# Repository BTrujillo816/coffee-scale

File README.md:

# ECET 430 Project: Digital Coffee Scale

This is a project for NJIT's ECET 430 - Electronics Manufacturing class.

## Purpose

This digital coffee scale will display weight measurements, flow rate, and include a built-in timer. It will also be able to send brew parameters through WiFi or Bluetooth to an App or other interface.

## Repo Layout

- `hardware` KiCad project with schematic, pcb layout, plots, drawings
- `software` ESP32 firmware and Arduino IDE setup
- `documentation` Technical documentation and user manual
- `logbook` Markdown files for progress updates

## Usage

See the [user documentation](documentation/UserDocumentation.md).

## Design

See the [design decision document](documentation/DesignDecisions.md).

## Credit

This project was made possible by borrowing from great designs, including:

- ABC's wearable widget, https://github.com/example/project
- XYZ's battery management, https://github.com/example/otherproject

## Author

Written by Brandon Trujillo and Miguel Takinan, 2024

## License

This work is available under the [Creative Commons Attribution-ShareAlike License 4.0](https://en.wikipedia.org/wiki/Wikipedia:Text_of_the_Creative_Commons_Attribution-ShareAlike_4.0_International_License). A local copy is available at [LICENSE.md](LICENSE.md).

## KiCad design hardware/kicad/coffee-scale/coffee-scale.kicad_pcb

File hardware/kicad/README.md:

# Digital Coffee Scale KiCad Project

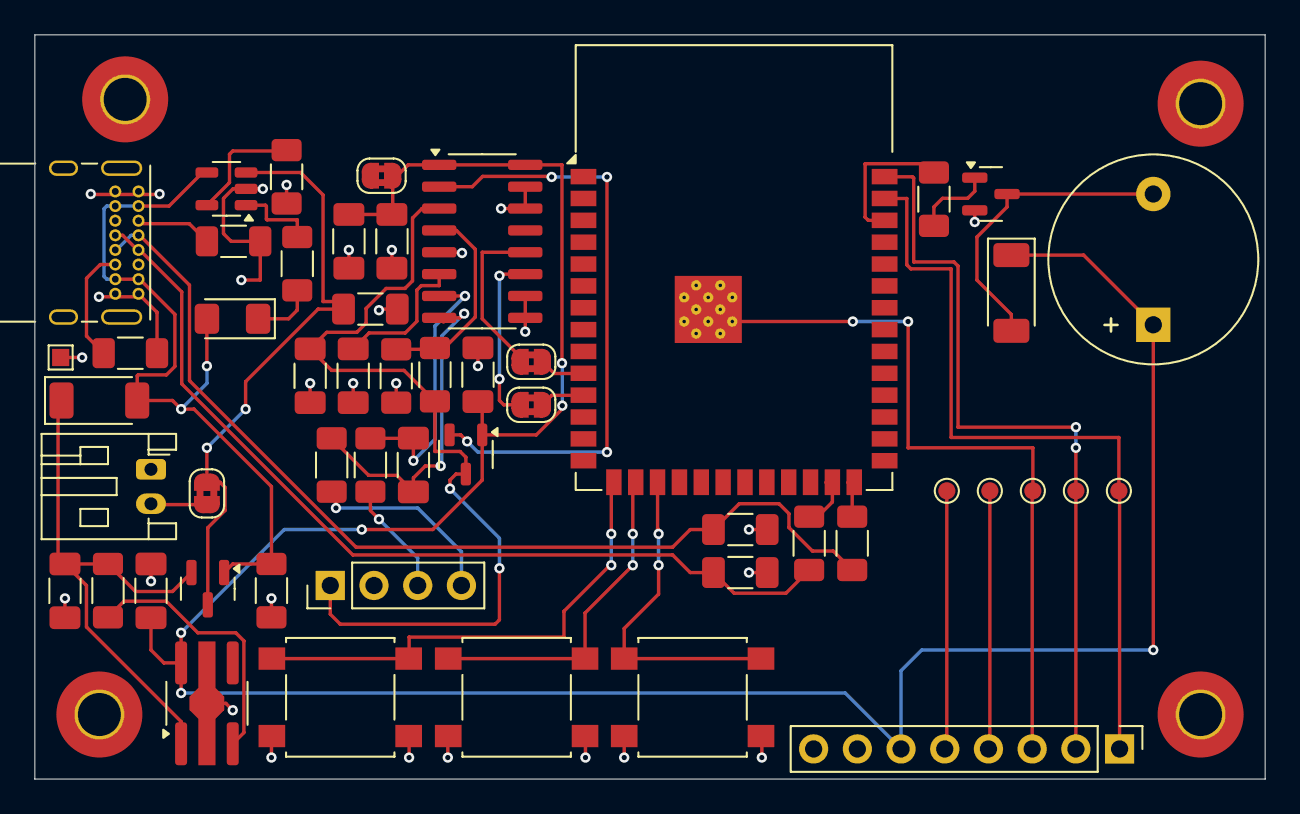
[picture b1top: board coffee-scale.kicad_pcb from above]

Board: 2 copper layers, 71.5 x 43.2 mm, 56 parts (0 on the bottom side), 39 nets.

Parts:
C1, C2, C3, C4, C5, C6: 10uF; C_1206_3216Metric_Pad1.33x1.80mm_HandSolder
C7, C9: 100nF; C_1206_3216Metric_Pad1.33x1.80mm_HandSolder
C8: 10uf; C_1206_3216Metric_Pad1.33x1.80mm_HandSolder
C10, C11: 20p; C_1206_3216Metric_Pad1.33x1.80mm_HandSolder
D1: D_SOD-128
D2: LED; LED_1206_3216Metric_Pad1.42x1.75mm_HandSolder
D4: D_Schottky_Filled; D_SOD-128
H1, H2, H3, H4: MountingHole; MountingHole_2.5mm_Pad_TopBottom
J1: Conn_01x08; PinHeader_1x08_P2.54mm_Vertical
J2: Conn_01x04; PinHeader_1x04_P2.54mm_Vertical
J3: Conn_01x02; JST_PH_S2B-PH-K_1x02_P2.00mm_Horizontal
J4: USB C; USB_C_Receptacle_GCT_USB4085
JP1, JP2, JP3, JP4: SolderJumper_2_Bridged; SolderJumper-2_P1.3mm_Bridged2Bar_RoundedPad1.0x1.5mm
LS1: Speaker; Buzzer_12x9.5RM7.6
Q1: DMG3415U; SOT-23
Q2: S8550; SOT-23-3
Q3: BSS138; SOT-23
R1, R2: 100k; R_1206_3216Metric_Pad1.30x1.75mm_HandSolder
R3, R4, R9, R10: 5.1k; R_1206_3216Metric_Pad1.30x1.75mm_HandSolder
R5, R6, R7, R8: 100; R_1206_3216Metric_Pad1.30x1.75mm_HandSolder
R11: 10k; R_1206_3216Metric_Pad1.30x1.75mm_HandSolder
R12, R13: 22; R_1206_3216Metric_Pad1.30x1.75mm_HandSolder
SW1, SW2, SW3: SW_Push; SW_SPST_B3S-1000
TP1, TP2, TP3, TP4, TP5: TestPoint_Small; TestPoint_Pad_D1.0mm
TP6: TestPoint_Small; TestPoint_Pad_1.0x1.0mm
U1: ESP32-S3; ESP32-S3-WROOM-1
U2: HX711; SOP-16_3.9x9.9mm_P1.27mm
U3: MCP73832-5-OT; SOT-23-5
U4: AP2112/RT9080-3.3; SOT-89-5_Handsoldering

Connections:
3.3V: C2.1, C4.1, C5.1, C6.1, D4.1 (K), J1.6, JP1.1 (A), LS1.1, Q2.1 (E), U2.1 (VSUP), U2.16 (DVDD), U4.5 (OUT)
/BEEP: R11.2, U1.38 (GPIO33)
/BUT1: SW1.1, U1.15 (GPIO10)
/BUT2: SW2.1, U1.16 (GPIO11)
/BUT3: SW3.1, U1.17 (GPIO12)
/CLK: J1.4, TP4.1
/CS: J1.1, TP1.1, U1.39 (GPIO34)
/D+: C11.1, J4.A6 (D+), J4.B6 (D+), R13.1
/D-: C10.2, J4.A7 (D-), J4.B7 (D-), R12.2
/DATA: J1.5, TP5.1
/D/C: J1.3, TP3.1, U1.41 (GPIO36)
/E+: C8.1, J2.1, Q2.3 (C), R7.2, U2.3 (AVDD)
/RST: J1.2, TP2.1, U1.40 (GPIO35)
/S+: J2.4, R6.1
/S-: J2.3, R5.1
GND: C1.2, C2.2, C3.2, C4.2, C5.2, C6.2, C8.2, C9.1, C10.1, C11.2, J1.8, J2.2, J3.1, J4.A1 (GND), J4.A12 (GND), J4.B1 (GND), J4.B12 (GND), J4.S1 (SHIELD), Q3.2 (S), R2.2, R4.2, R8.1, R9.2, R10.2, SW1.2, SW2.2, SW3.2, TP6.1, U2.5 (AGND), U2.9 (INB-), U2.10 (INB+), U2.14 (XI), U2.15 (RATE), U3.2 (V_{SS}), U4.2 (GND)
unnamed: C1.1, D1.1 (K), Q1.2 (S), R1.1, U4.1 (IN)
unnamed: D2.1 (K), R3.1
unnamed: D4.2 (A), LS1.2, Q3.3 (D)
unnamed: J3.2, JP4.1 (A)
unnamed: J4.A5 (CC1), R10.1
unnamed: J4.B5 (CC2), R9.1
unnamed: JP2.1 (A), U2.12 (DOUT)
unnamed: JP2.2 (B), U1.10 (GPIO5)
unnamed: JP3.1 (A), U1.11 (GPIO6)
unnamed: JP3.2 (B), U2.11 (PD_SCK)
unnamed: Q2.2 (B), U2.2 (BASE)
unnamed: Q3.1 (G), R11.1
unnamed: R12.1, U1.25 (GPIO19/USB_D-)
unnamed: R13.2, U1.26 (GPIO20/USB_D+)
unnamed: C7.2, R6.2, U2.8 (INA+)
unnamed: C7.1, R5.2, U2.7 (INA-)
unnamed: C9.2, U2.6 (VBG)
unnamed: R7.1, R8.2, U2.4 (VFB)
unnamed: R4.1, U3.5 (PROG)
unnamed: R3.2, U3.1 (STAT)
unnamed: R1.2, U4.3 (EN)
VBAT: C3.1, JP4.2 (B), Q1.3 (D), U3.3 (V_{BAT})
VBUS: D1.2 (A), D2.2 (A), J4.A4 (VBUS), J4.A9 (VBUS), J4.B4 (VBUS), J4.B9 (VBUS), Q1.1 (G), R2.1, U3.4 (V_{DD})

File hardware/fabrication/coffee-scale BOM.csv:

"Reference","Value","Footprint","Qty","MPN"
"C1,C2,C3,C4,C5,C6","10uF","Capacitor_SMD:C_1206_3216Metric_Pad1.33x1.80mm_HandSolder","6",""
"C7,C9","100nF","Capacitor_SMD:C_1206_3216Metric_Pad1.33x1.80mm_HandSolder","2",""
"C8","10uf","Capacitor_SMD:C_1206_3216Metric_Pad1.33x1.80mm_HandSolder","1",""
"C10,C11","20p","Capacitor_SMD:C_1206_3216Metric_Pad1.33x1.80mm_HandSolder","2",""
"D1","~","Diode_SMD:D_SOD-128","1","PMEG4050EP,115"
"D2","LED","LED_SMD:LED_1206_3216Metric_Pad1.42x1.75mm_HandSolder","1",""
"D4","D_Schottky_Filled","Diode_SMD:D_SOD-128","1","DMG2301L-7 "
"J1","Conn_01x08","Connector_PinHeader_2.54mm:PinHeader_1x08_P2.54mm_Vertical","1",""
"J2","Conn_01x04","Connector_PinHeader_2.54mm:PinHeader_1x04_P2.54mm_Vertical","1",""
"J3","Conn_01x02","Connector_JST:JST_PH_S2B-PH-K_1x02_P2.00mm_Horizontal","1",""
"J4","USB C","Connector_USB:USB_C_Receptacle_GCT_USB4085","1","USB4085-GF-A"
"LS1","Speaker","Buzzer_Beeper:Buzzer_12x9.5RM7.6","1",""
"Q1","DMG3415U","Package_TO_SOT_SMD:SOT-23","1","DMG2301L-7"
"Q2","S8550","Package_TO_SOT_SMD:SOT-23-3","1","S8550"
"Q3","BSS138","Package_TO_SOT_SMD:SOT-23","1","BSS138"
"R1,R2","100k","Resistor_SMD:R_1206_3216Metric_Pad1.30x1.75mm_HandSolder","2",""
"R3,R4,R9,R10","5.1k","Resistor_SMD:R_1206_3216Metric_Pad1.30x1.75mm_HandSolder","4",""
"R5,R6,R7,R8","100","Resistor_SMD:R_1206_3216Metric_Pad1.30x1.75mm_HandSolder","4",""
"R11","10k","Resistor_SMD:R_1206_3216Metric_Pad1.30x1.75mm_HandSolder","1",""
"R12,R13","22","Resistor_SMD:R_1206_3216Metric_Pad1.30x1.75mm_HandSolder","2",""
"SW1,SW2,SW3","SW_Push","Button_Switch_SMD:SW_SPST_Omron_B3FS-105xP","3",""
"TP1,TP2,TP3,TP4,TP5,TP6","TestPoint_Small","-- mixed values --","6",""
"U1","ESP32-S3","RF_Module:ESP32-S3-WROOM-1","1","ESP32-S3-WROOM-1-N16"
"U2","HX711","Package_SO:SOP-16_3.9x9.9mm_P1.27mm","1","HX711"
"U3","MCP73832-5-OT","Package_TO_SOT_SMD:SOT-23-5","1","MCP73832T-5ACI/OT"
"U4","AP2112/RT9080-3.3","Package_TO_SOT_SMD:SOT-89-5_Handsoldering","1","AP2112R5-3.3TRG1"

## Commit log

2024-09-04 Setup initial file structure
    File structure based on Fitness Tracker example project
2024-09-04 Change license
    Changes license from MIT to Creative Commons
2024-09-04 Update README.md
    Edited example README.md to better suit project.
2024-09-04 Create logbook
2024-09-04 Create logbook folder
2024-09-05 Create ProjectTemplate.md
    Creates the first iteration of the Project Template
2024-09-06 test
    spacing
2024-09-06 test
    test
2024-09-06 fixes
    spacing
2024-09-09 Change name from Project Template 2 to ProjectTemplate2
2024-09-09 Update ProjectTemplate.md with glossary definitions
2024-09-15 file name edit
2024-09-15 Update assets to include datasheets
    Includes datasheets for potential major component selection
2024-09-20 Update Log Book
    Creates logbooks file and inputs first entry
2024-09-21 Update logbook
    Adds an extra task and also changes formatting based on tackled issues.
2024-09-23 Update logbook
    Changes naming convention e.g. dd-mm-yy for logbook files and adds 09-23-24.
2024-09-24 Adds KiCAD Project file to KiCAD folder
2024-09-24 Update Schematic
2024-09-24 Added load cell symbol and made connection to the HX711
2024-09-24 Update on KiCad
2024-09-24 Add/delete
2024-09-28 Rename DesignDocument_MajorMovingParts.md to DesignDecisions.md
2024-10-01 Update Schematic
    Creates individual sheets for different major moving part sections
2024-10-03 Update 10-02-24.md
    Contains image and image folder
2024-10-03 Update 10-02-24.md
    Changes formatting of image
2024-10-15 Add .ino files
2024-10-16 Update logbook files to follow a consistent layout
2024-10-29 Create 10-29-24.md
    Also updates 10-22-24.md
2024-10-31 Create 10-30-24.md
    Also add SSD1306 datasheet
2024-10-31 Update 10-30-24.md
    Update 10-30-24.md to include tasks that need to be done
2024-11-09 Miscellaneous edits
2024-11-10 Update Stage 1 & Stage 2
2024-11-13 Update schematic to include USB-C connector
2024-11-13 Create logbook 11-12-24.md and update schematic
2024-11-14 Code with complete funtionality
    - Sounds when buttons are pressed
    - Tare
    - Timer
    - Deep sleep
    - Flow rate
2024-11-14 Deep sleep sample code from webite
2024-11-14 Test for the timer functionality
2024-11-14 edit name
2024-11-14 Update software format
2024-11-14 Organize software section
2024-11-14 Various updates
2024-11-14 Minor logbook edits
2024-12-10 Add files via upload
    Update version with PCB design complete with traces
2024-12-11 PCB Update
2024-12-12 Update footprints
2024-12-16 logbook and PCB routing edits
2024-12-18 Update fp-info-cache
2024-12-19 Update Coffee_Scale_Complete_Functionality.ino
    Stabilize flow rate and weight display
2024-12-19 Add webserver test code
